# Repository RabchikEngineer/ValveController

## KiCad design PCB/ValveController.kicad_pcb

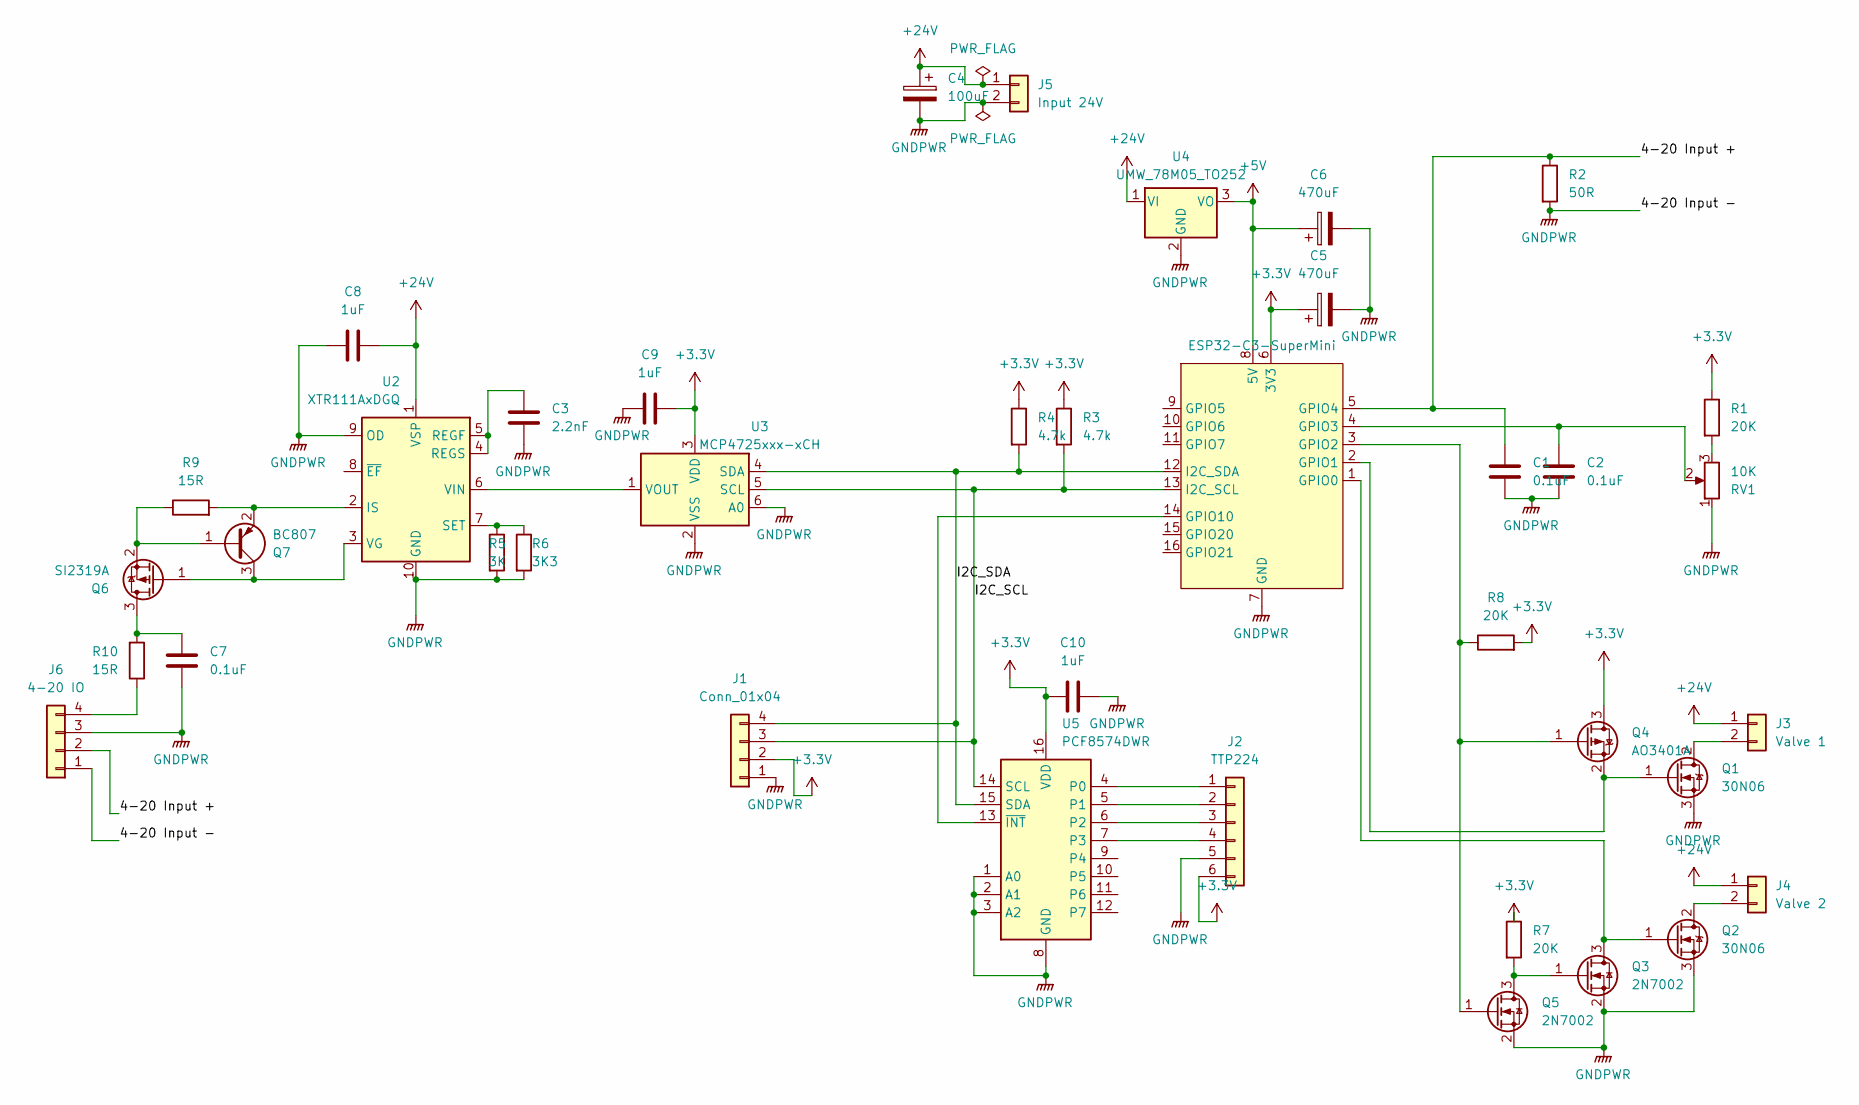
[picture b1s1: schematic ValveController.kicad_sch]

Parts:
C1, C2, C7: 0.1uF; C_0603_1608Metric_Pad1.08x0.95mm_HandSolder
C3: 2.2nF; C_0603_1608Metric_Pad1.08x0.95mm_HandSolder
C4: 100uF; C_Radial_D8.0mm_H11.5mm_P3.50mm
C5, C6: 470uF; C_Radial_D6.3mm_H11.0mm_P2.50mm
C8, C9, C10: 1uF; C_0603_1608Metric_Pad1.08x0.95mm_HandSolder
J1: Conn_01x04; JST_XH_B4B-XH-A_1x04_P2.50mm_Vertical
J2: TTP224; JST_XH_B6B-XH-A_1x06_P2.50mm_Vertical
J3: Valve 1; SolderWire-0.5sqmm_1x02_P4.6mm_D0.9mm_OD2.1mm
J4: Valve 2; SolderWire-0.5sqmm_1x02_P4.6mm_D0.9mm_OD2.1mm
J5: Input 24V; JST_XH_B2B-XH-A_1x02_P2.50mm_Vertical
J6: 4-20 IO; JST_XH_B4B-XH-A_1x04_P2.50mm_Vertical
Q1, Q2: 30N06; TO-252-2
Q3, Q5: 2N7002; SOT-23
Q4: AO3401A; SOT-23
Q6: SI2319A; SOT-23
Q7: BC807; SOT-23
R1, R7, R8: 20K; R_0805_2012Metric_Pad1.20x1.40mm_HandSolder
R2: 50R; R_0805_2012Metric_Pad1.20x1.40mm_HandSolder
R3, R4: 4.7k; C_0603_1608Metric_Pad1.08x0.95mm_HandSolder
R5: 3K; C_0603_1608Metric_Pad1.08x0.95mm_HandSolder
R6: 3K3; C_0603_1608Metric_Pad1.08x0.95mm_HandSolder
R9, R10: 15R; C_0603_1608Metric_Pad1.08x0.95mm_HandSolder
RV1: 10K; SolderWire-0.5sqmm_1x03_P4.6mm_D0.9mm_OD2.1mm
U1: ESP32-C3-SuperMini
U2: XTR111AxDGQ; MSOP-10-1EP_3x3mm_P0.5mm_EP2.2x3.1mm_Mask1.83x1.89mm_Therma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
U3: MCP4725xxx-xCH; SOT-23-6
U4: UMW_78M05_TO252; TO-252-2
U5: PCF8574DWR; SOIC-16W_7.5x10.3mm_P1.27mm

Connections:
+3.3V: C5.1, C9.2, C10.1, J1.2, J2.6, Q4.3 (D), R1.1, R3.1, R4.1, R7.1, R8.2, U1.6 (3V3), U3.3 (VDD), U5.16 (VDD)
+5V: C6.1, U1.8 (5V), U4.3 (VO)
+24V: C4.1, C8.2, J3.1, J4.1, J5.1, U2.1 (VSP), U4.1 (VI)
/4-20 Input +: C1.1, J6.2, R2.1, U1.5 (GPIO4)
/I2C_SCL: J1.3, R3.2, U1.13 (I2C_SCL), U3.5 (SCL), U5.14 (SCL)
/I2C_SDA: J1.4, R4.2, U1.12 (I2C_SDA), U3.4 (SDA), U5.15 (SDA)
GNDPWR: C1.2, C2.2, C3.2, C4.2, C5.2, C6.2, C7.2, C8.1, C9.1, C10.2, J1.1, J2.5, J5.2, J6.1, J6.3, Q1.3 (S), Q2.3 (S), Q3.2 (S), Q5.2 (S), R2.2, R5.2, R6.2, RV1.1, U1.7 (GND), U2.9 (OD), U2.10 (GND), U2.11 (GND), U3.2 (VSS), U3.6 (A0), U4.2 (GND), U5.1 (A0), U5.2 (A1), U5.3 (A2), U5.8 (GND)
unnamed: J2.1, U5.4 (P0)
unnamed: J2.2, U5.5 (P1)
unnamed: J2.3, U5.6 (P2)
unnamed: J2.4, U5.7 (P3)
unnamed: J3.2, Q1.2 (D)
unnamed: J4.2, Q2.2 (D)
unnamed: J6.4, R10.1
unnamed: Q1.1 (G), Q4.2 (S), U1.2 (GPIO1)
unnamed: Q2.1 (G), Q3.3 (D), U1.1 (GPIO0)
unnamed: Q3.1 (G), Q5.3 (D), R7.2
unnamed: Q4.1 (G), Q5.1 (G), R8.1, U1.3 (GPIO2)
unnamed: C7.1, Q6.3 (D), R10.2
unnamed: Q6.1 (G), Q7.3 (C), U2.3 (VG)
unnamed: Q6.2 (S), Q7.1 (B), R9.1
unnamed: Q7.2 (E), R9.2, U2.2 (IS)
unnamed: R1.2, RV1.3
unnamed: C2.1, RV1.2, U1.4 (GPIO3)
unnamed: U1.14 (GPIO10), U5.13 (~INT)
unnamed: C3.1, U2.4 (REGS), U2.5 (REGF)
unnamed: R5.1, R6.1, U2.7 (SET)
unnamed: U2.6 (VIN), U3.1 (VOUT)

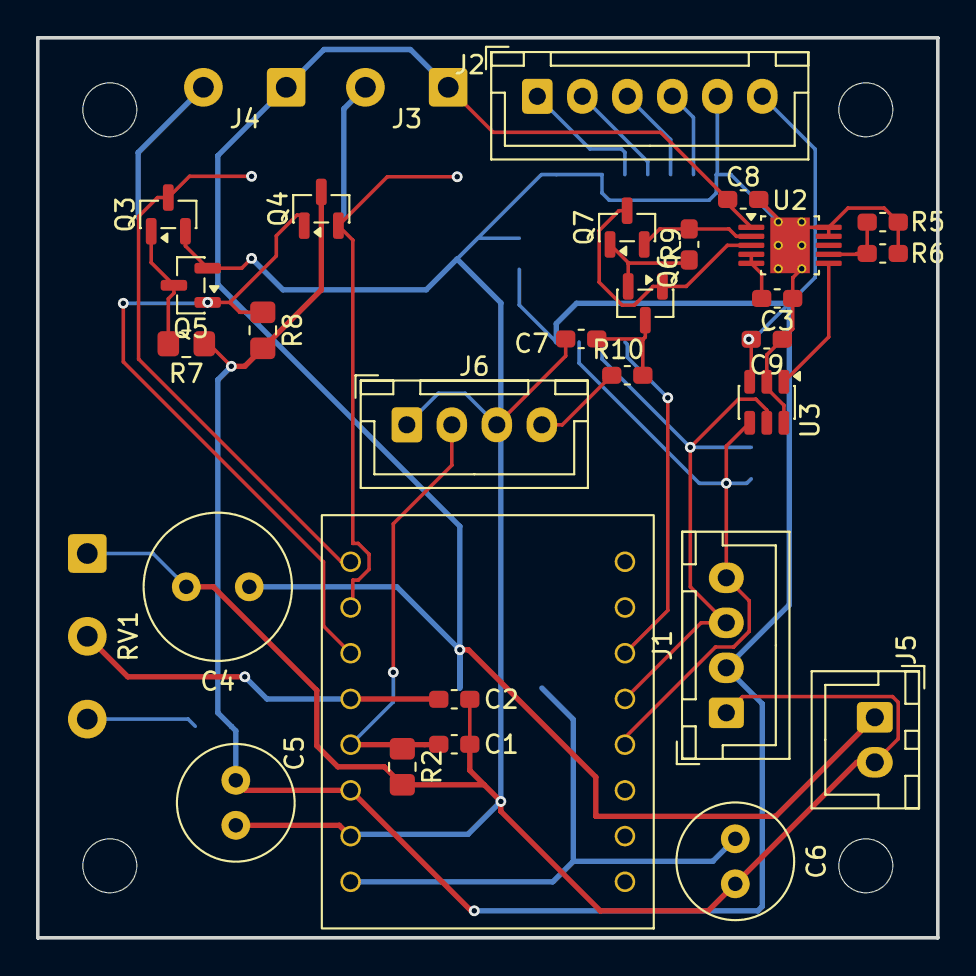
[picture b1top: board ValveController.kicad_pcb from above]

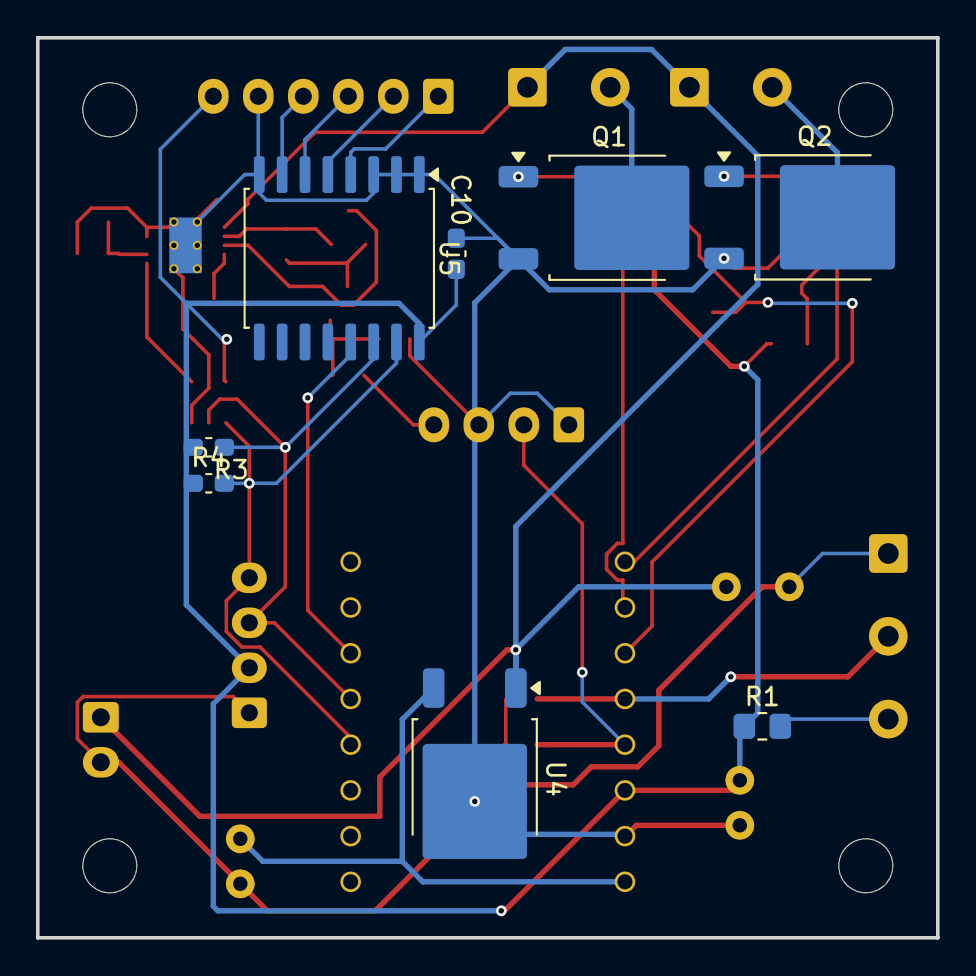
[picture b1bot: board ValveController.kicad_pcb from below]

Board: 2 copper layers, 50.0 x 50.0 mm, 39 parts (8 on the bottom side), 28 nets.

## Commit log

2025-11-08 One-shot version backup
2025-11-09 Continous adc measurement
2025-11-09 Added pwm for valves, increaced precision via PID
2025-11-17 PID coeff can be setted via usb
2025-12-03 moved files
2025-12-03 Split code to modules
2025-12-03 Include PCB project
2025-12-08 Scheme and PCB updates
2025-12-13 Backup before refactoring
2025-12-16 refactoring
2026-02-01 All components tested, backup before code refactoring
2026-02-03 UI v0.5
2026-03-13 UI v1.0 + calibration testing
2026-03-28 Valve V1.1 improved ui, added calibration
2026-04-01 Valve v1.1.1
2026-04-01 Code v1.1.2
